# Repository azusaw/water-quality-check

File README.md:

# water-check-app

## Live URL

https://water-quality-check-ab451.web.app/

## Members

Azusa Watanabe
Didier van Os
Javier Gonzalez

## .env file

Create `.env` file in the _vite_ directory. The values for these variables can be found in the [firebase console](https://console.firebase.google.com/) (see Project Settings). They are formatted as follows (values have been modified/redacted):

```
VITE_FIREBASE_API_KEY=AIzaXXXXXXXXXXXXXXXXXXXXZ8Hyg
VITE_FIREBASE_AUTH_DOMAIN=water-quality-check-ab451.firebaseapp.com
VITE_FIREBASE_PROJECT_ID=water-quality-check-ab451
VITE_FIREBASE_STORAGE_BUCKET=water-quality-check-ab451.appspot.com
VITE_FIREBASE_SENDER_ID=1052XXXXXX34
VITE_FIREBASE_APP_ID=1:105XXXXX934:web:6f9XXXXXXXXX36857
VITE_FIREBASE_MEASUREMENT_ID=G-7CXXXXXJ
```

## Start web app in local

```commandline
cd ./vite
npm install
npm run dev
```

## Deploy on firebase-hosting

```commandline
cd ./vite
npm run build
firebase deploy
```

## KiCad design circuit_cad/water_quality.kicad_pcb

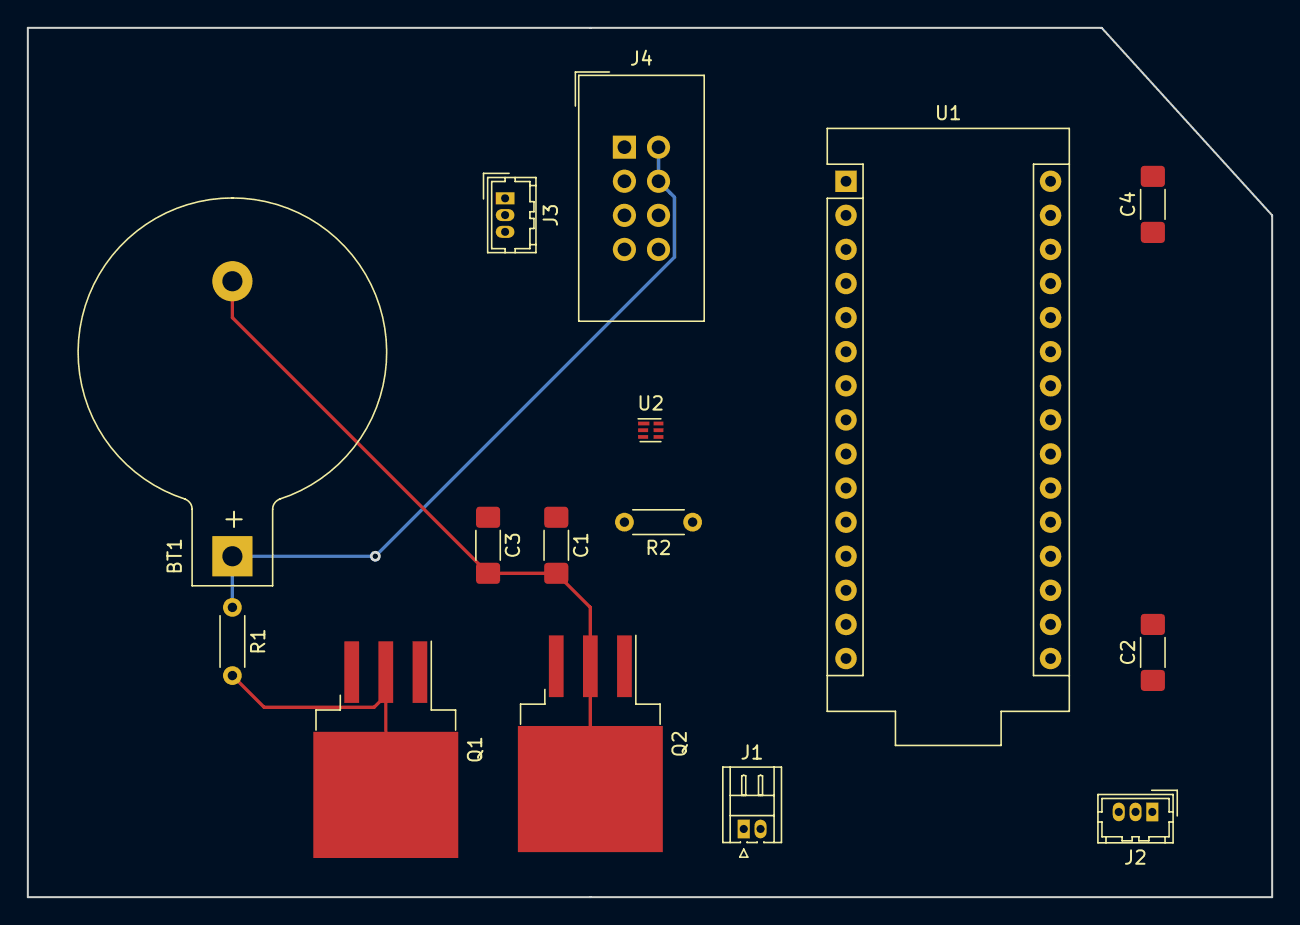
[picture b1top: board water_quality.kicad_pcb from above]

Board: 2 copper layers, 92.7 x 64.8 mm, 15 parts (0 on the bottom side), 13 nets.

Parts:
BT1: Battery_Cell; BatteryHolder_Keystone_103_1x20mm
C1, C2, C3, C4: 0u1; C_1806_4516Metric_Pad1.57x1.80mm_HandSolder
J1: Conn_01x02; Hirose_DF13-02P-1.25DS_1x02_P1.25mm_Horizontal
J2: Conn_01x03_MountingPin; Hirose_DF13-03P-1.25DSA_1x03_P1.25mm_Vertical
J3: Conn_01x03; Hirose_DF13-03P-1.25DSA_1x03_P1.25mm_Vertical
J4: Conn_02x04_Counter_Clockwise; IDC-Header_2x04_P2.54mm_Vertical
Q1: Q_NMOS_CHG; TO-263-3_TabPin2
Q2: Q_NMOS_DSG; TO-263-3_TabPin2
R1: 2K2; R_Axial_DIN0204_L3.6mm_D1.6mm_P5.08mm_Horizontal
R2: 330; R_Axial_DIN0204_L3.6mm_D1.6mm_P5.08mm_Horizontal
U1: Arduino_Nano_Every
U2: BQ297xy; WSON-6_1.5x1.5mm_P0.5mm

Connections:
3v3: BT1.1, C2.2, C3.1, C4.2, J2.2, J4.2, J4.4, R1.1, R2.1, U1.17, U1.30, U2.6
Earth: BT1.2, C1.2, C2.1, C3.2, C4.1, J2.3, J4.8, Q2.2, U1.4, U1.29, U2.4
unnamed: C1.1, R2.2, U2.5
unnamed: Q1.1, Q2.1
unnamed: Q1.2, R1.2
unnamed: Q1.3, U2.2
unnamed: Q2.3, U2.3
gp0: J3.2, J4.6
gp2: J3.3, J4.7
rst: J3.1, J4.3
rxd: J4.5, U1.2
s: J2.1, U1.20
txd: J4.1, U1.1

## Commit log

2023-02-21 initial commit: firebase function
2023-02-25 rename files
2023-02-25 commit next template
2023-03-02 Create basic leaflet map demo
2023-03-19 use react-router-dom
2023-03-19 create get firebase data function
2023-03-20 replace data to firebase data
2023-03-20 use Material UI
2023-03-20 organise url and components
2023-03-20 create entry form
2023-03-20 deploy app in firebase
2023-03-20 create formik form and map
2023-03-20 stub out points service
2023-03-20 create alert after register
2023-03-20 resolve import error
2023-03-20 connect with google login info
2023-03-20 modify showing info
2023-03-21 make respoisive
2023-03-21 use google avater
2023-03-21 use current location
2023-03-21 remove auth page
2023-03-21 change favicon
2023-03-21 change map marker color
2023-03-22 Correct/clarify README
2023-03-22 Restructure (localise unique components to pages)
2023-03-22 Use react-query for map data fetching
2023-03-22 Improve popup details
2023-03-22 Add explainer popup to map point details
2023-03-22 Style map and add disclaimer, deprecate filter
2023-03-22 Make pH and TDS optional fields through select
2023-03-22 improve home
2023-03-22 improve form and map
2023-03-23 Add loading spinner to map
2023-03-23 Circuit Diagram Files
2023-03-23 3D Models and videos
2023-03-23 3D Models and Parts
2023-03-23 Refactor form using recommended formik component
2023-03-23 create header
2023-03-23 Fix savePoint draft object
2023-03-23 improve popup ui
2023-03-23 Create mock measurement device call
2023-03-23 Improve mock device fetching UI
2023-03-23 Add form reset option
2023-03-23 Reimplement device location
2023-03-23 modify css
2023-03-23 rename directory
2023-03-23 Final Schematic, PCB Layout and captures
2023-03-24 Setup basic info page
2023-03-24 modify header css
2023-03-24 fix infinite login loop
2023-03-24 create info btn to header
2023-03-24 fix wrong attribute
2023-03-24 remove unnecessary button
2023-03-24 add stroke in pin icon
2023-03-24 move header outside container
2023-03-24 Fix tooltip position bug
2023-03-24 Add info section - community projects
2023-03-24 add TDS in popup
2023-03-26 Implement scoring
2023-03-26 Implement zod validators for new form
2023-03-27 Add contaminants to form and marker
2023-03-27 Extract MapMarker
2023-03-27 Improve popup
2023-03-27 Minor popup improvements
2023-03-29 remove statements not used, modify header size
2023-03-29 changed tooltip icon position
2023-03-29 modify drinkability score caluculation
2023-03-29 make notification for safari, create logout button
2023-03-29 remove unnecessary files
2023-03-29 create neutral yellow pin
2023-03-29 edit attention text
